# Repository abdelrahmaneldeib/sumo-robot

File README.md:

# sumo-robot
Welcome to an exciting project that showcases the design and development of a Sumo robot tailored to meet the specific goals and requirements of our esteemed client This project not only emphasizes technical prowess but also ingenuity and creativity in engineering solutions.

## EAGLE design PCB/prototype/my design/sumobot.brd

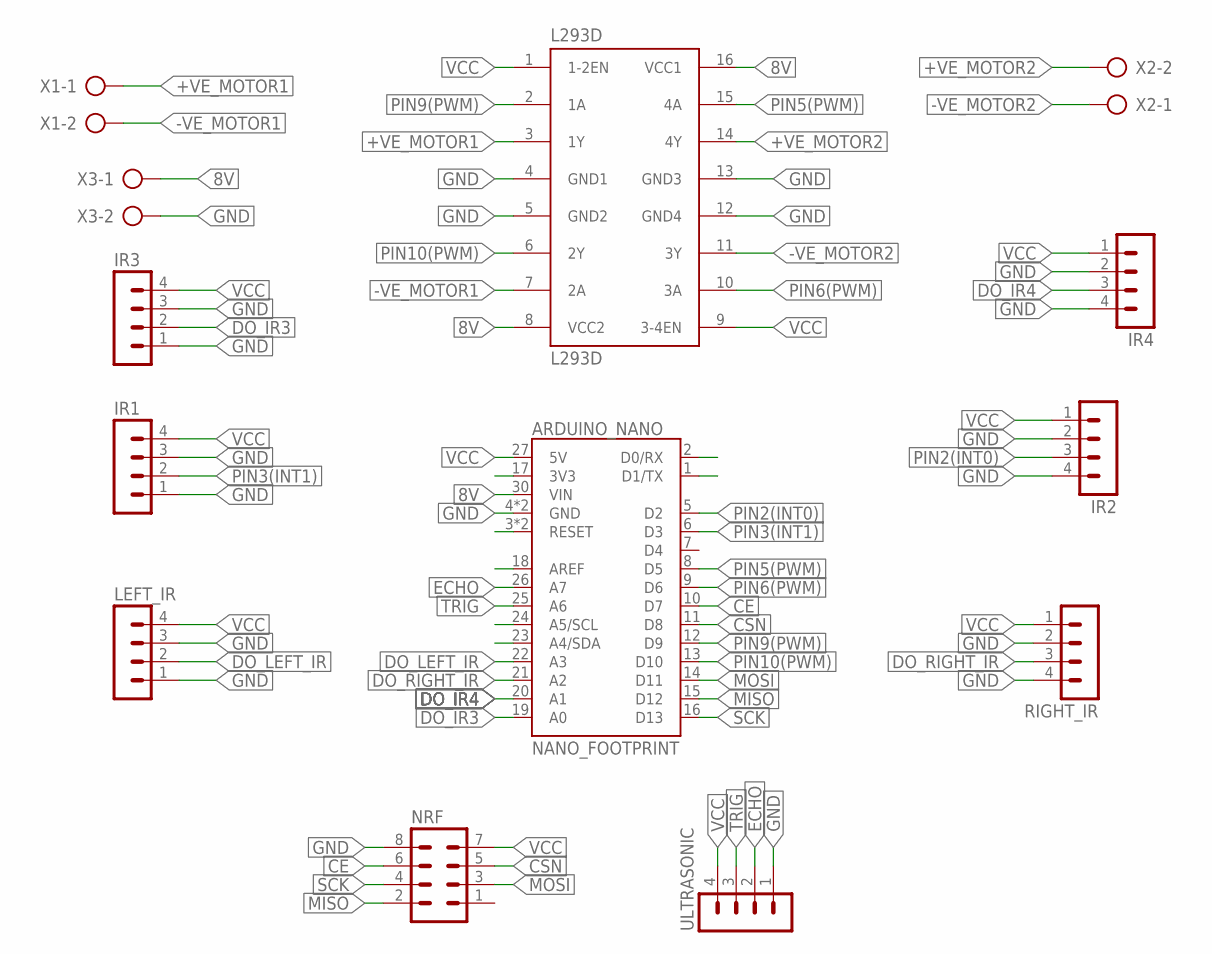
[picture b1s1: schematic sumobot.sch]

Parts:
ARDUINO_NANO: NANO_FOOTPRINT; NANO
IR1, IR2, IR3, IR4: MA04-1
L293D: L293D; DIL16
LEFT_IR: MA04-1
NRF: MA04-2
RIGHT_IR: MA04-1
ULTRASONIC: MA04-1
X1, X2, X3: AK500/2

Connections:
8V: ARDUINO_NANO.30 (VIN), L293D.8 (VCC2), L293D.16 (VCC1), X3.1
+VE_MOTOR1: L293D.3 (1Y), X1.1
+VE_MOTOR2: L293D.14 (4Y), X2.2
-VE_MOTOR1: L293D.7 (2A), X1.2
-VE_MOTOR2: L293D.11 (3Y), X2.1
CE: ARDUINO_NANO.10 (D7), NRF.6
CSN: ARDUINO_NANO.11 (D8), NRF.5
DO_IR3: ARDUINO_NANO.19 (A0), IR3.2
DO_IR4: ARDUINO_NANO.20 (A1), IR4.3
DO_LEFT_IR: ARDUINO_NANO.22 (A3), LEFT_IR.2
DO_RIGHT_IR: ARDUINO_NANO.21 (A2), RIGHT_IR.3
ECHO: ARDUINO_NANO.26 (A7), ULTRASONIC.2
GND: ARDUINO_NANO.4 (GND), ARDUINO_NANO.29 (GND), IR1.1, IR1.3, IR2.2, IR2.4, IR3.1, IR3.3, IR4.2, IR4.4, L293D.4 (GND1), L293D.5 (GND2), L293D.12 (GND4), L293D.13 (GND3), LEFT_IR.1, LEFT_IR.3, NRF.8, RIGHT_IR.2, RIGHT_IR.4, ULTRASONIC.1, X3.2
MISO: ARDUINO_NANO.15 (D12), NRF.2
MOSI: ARDUINO_NANO.14 (D11), NRF.3
unnamed: ARDUINO_NANO.3 (RESET), ARDUINO_NANO.28 (RESET)
PIN2(INT0): ARDUINO_NANO.5 (D2), IR2.3
PIN3(INT1): ARDUINO_NANO.6 (D3), IR1.2
PIN5(PWM): ARDUINO_NANO.8 (D5), L293D.15 (4A)
PIN6(PWM): ARDUINO_NANO.9 (D6), L293D.10 (3A)
PIN9(PWM): ARDUINO_NANO.12 (D9), L293D.2 (1A)
PIN10(PWM): ARDUINO_NANO.13 (D10), L293D.6 (2Y)
SCK: ARDUINO_NANO.16 (D13), NRF.4
TRIG: ARDUINO_NANO.25 (A6), ULTRASONIC.3
VCC: ARDUINO_NANO.27 (5V), IR1.4, IR2.1, IR3.4, IR4.1, L293D.1 (1-2EN), L293D.9 (3-4EN), LEFT_IR.4, NRF.7, RIGHT_IR.1, ULTRASONIC.4

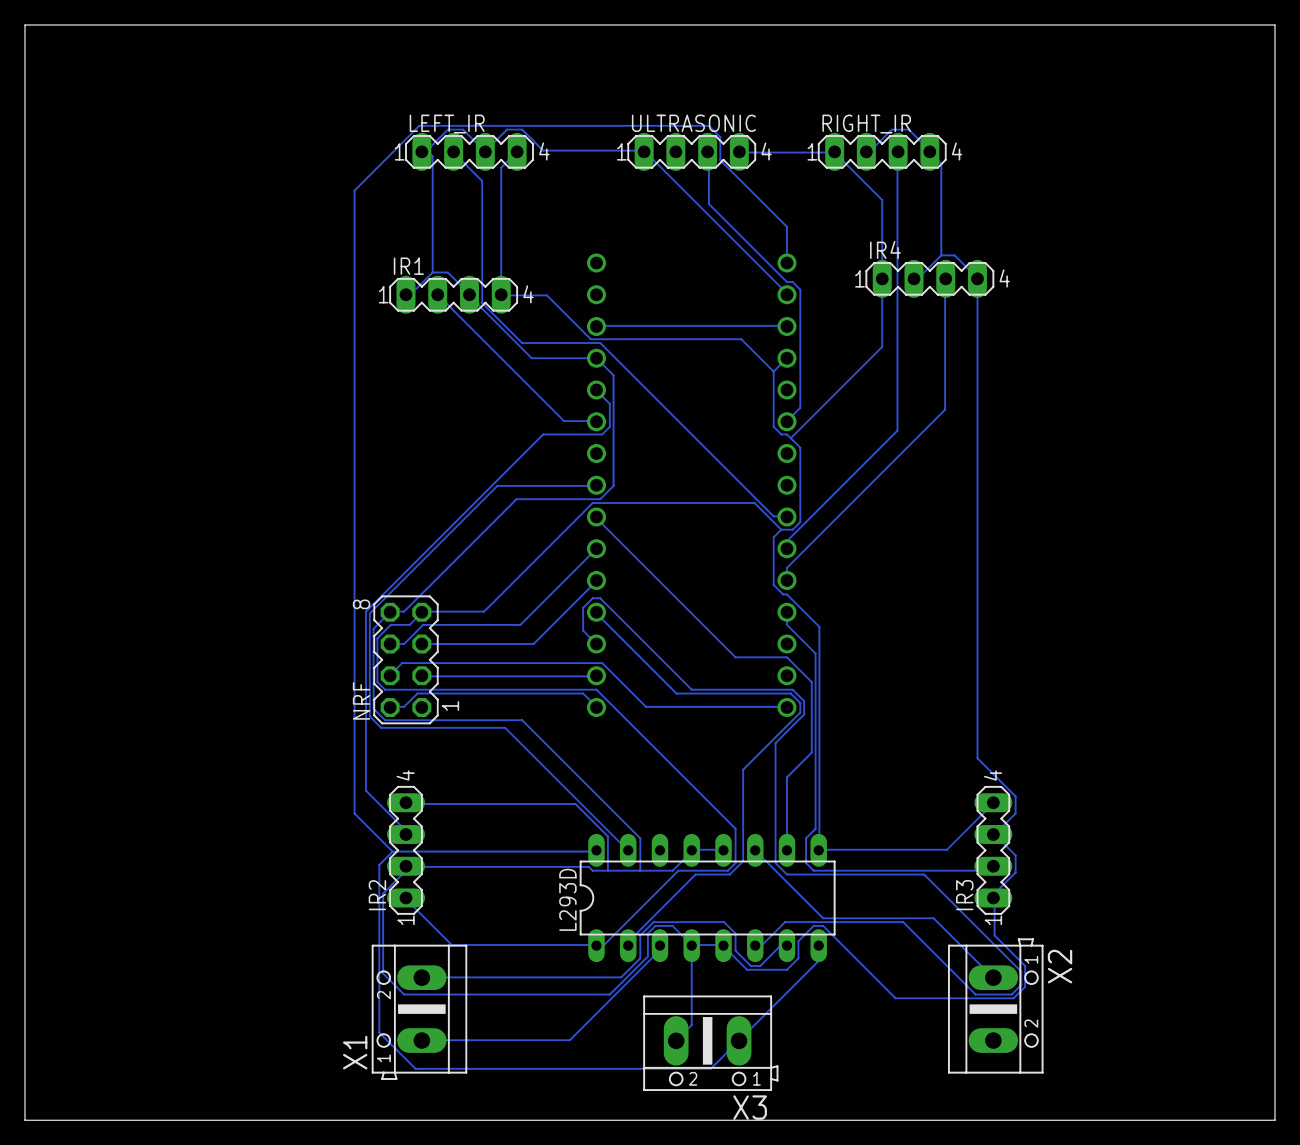
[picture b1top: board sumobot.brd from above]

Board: 2 copper layers, 100.0 x 87.6 mm, 13 parts (0 on the bottom side), 25 nets.

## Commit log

2024-05-13 Done

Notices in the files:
parts and their libraries:
SparkFun-Boards: Licensing: Creative Commons ShareAlike 4.0 International - https://creativecommons.org/licenses/by-sa/4.0
